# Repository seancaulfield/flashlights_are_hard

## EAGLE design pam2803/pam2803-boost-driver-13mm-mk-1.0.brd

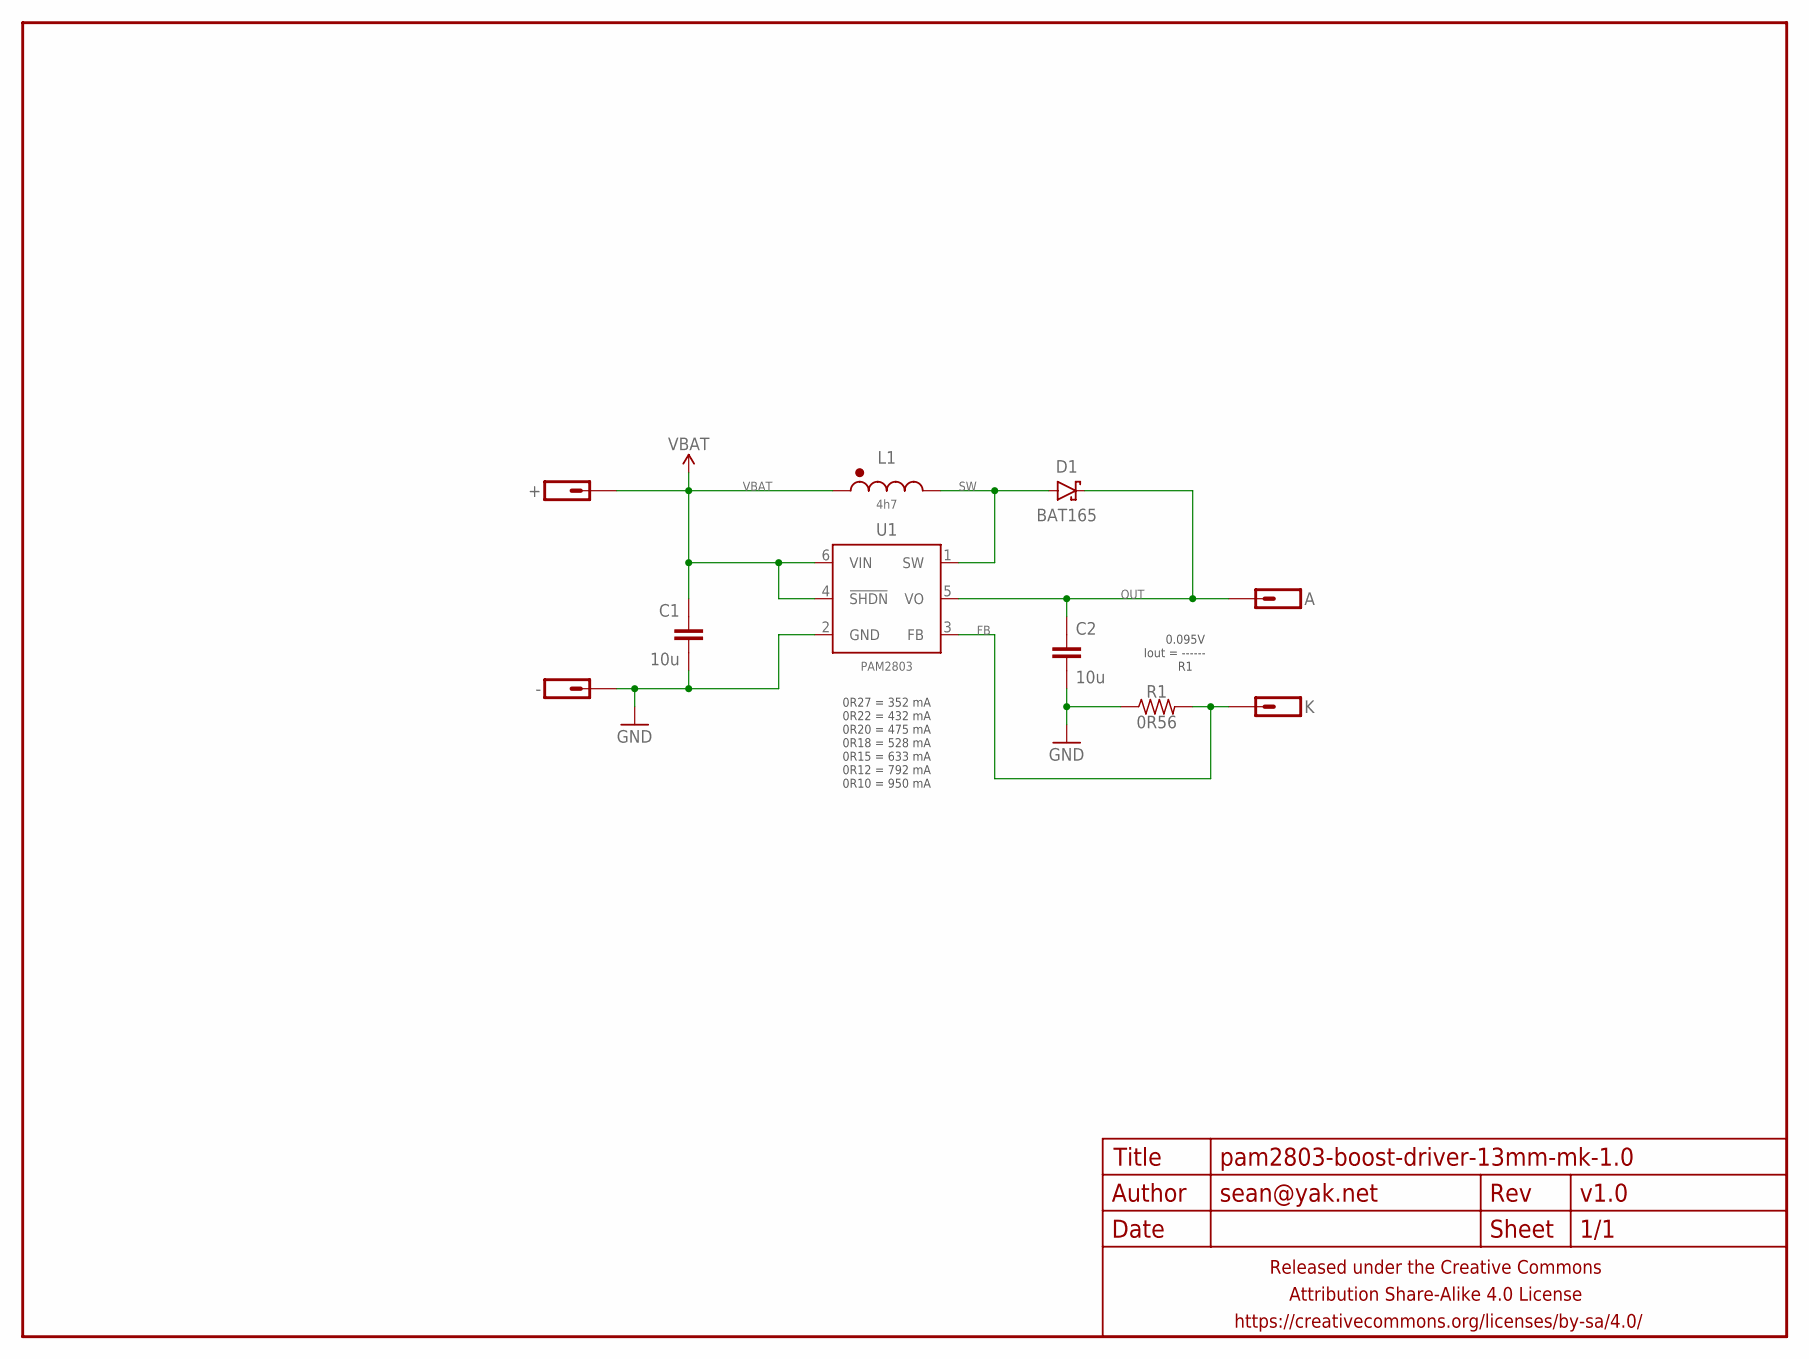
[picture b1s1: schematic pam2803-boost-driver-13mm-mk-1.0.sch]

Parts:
+: M01NOT-A-VIA-NOPE; 1X01_NOSILK_NOSTOP
-: M01NOT-A-VIA-NOPE; 1X01_NOSILK_NOSTOP
A: M01SMD-1.5MM-DIA-NS; 1X01-SMD-1.5MM-DIA-NS
C1, C2: 10u; C0805-TIGHTER
D1: BAT165; SOD323-SCHOTTKY
FRAME1: FRAME-LETTERNO_PACKAGE; DUMMY
K: M01SMD-1.5MM-DIA-NS; 1X01-SMD-1.5MM-DIA-NS
L1: 4h7; EPL2014
R1: 0R56; R0603-TIGHTER
U1: PAM2803; SOT23-6

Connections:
FB: K.P$1, R1.2, U1.3 (FB)
GND: -.P$1, C1.2, C2.2, R1.1, U1.2 (GND)
OUT: A.P$1, C2.1, D1.C, U1.5 (VO)
SW: D1.A, L1.P$2 (2), U1.1 (SW)
VBAT: +.P$1, C1.1, L1.P$1 (1), U1.4 (!SHDN), U1.6 (VIN)

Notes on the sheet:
0.095V Iout = ------ R1
0R27 = 352 mA 0R22 = 432 mA 0R20 = 475 mA 0R18 = 528 mA 0R15 = 633 mA 0R12 = 792 mA 0R10 = 950 mA

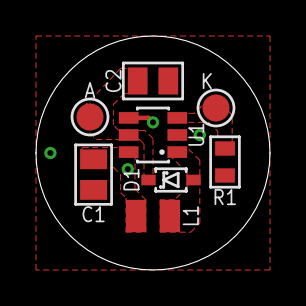
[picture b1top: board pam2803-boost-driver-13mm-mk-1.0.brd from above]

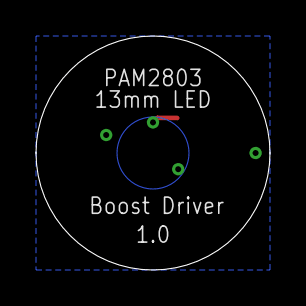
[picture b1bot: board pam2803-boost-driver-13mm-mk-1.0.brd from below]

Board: 2 copper layers, 13.0 x 13.0 mm, 11 parts (2 on the bottom side), 5 nets.

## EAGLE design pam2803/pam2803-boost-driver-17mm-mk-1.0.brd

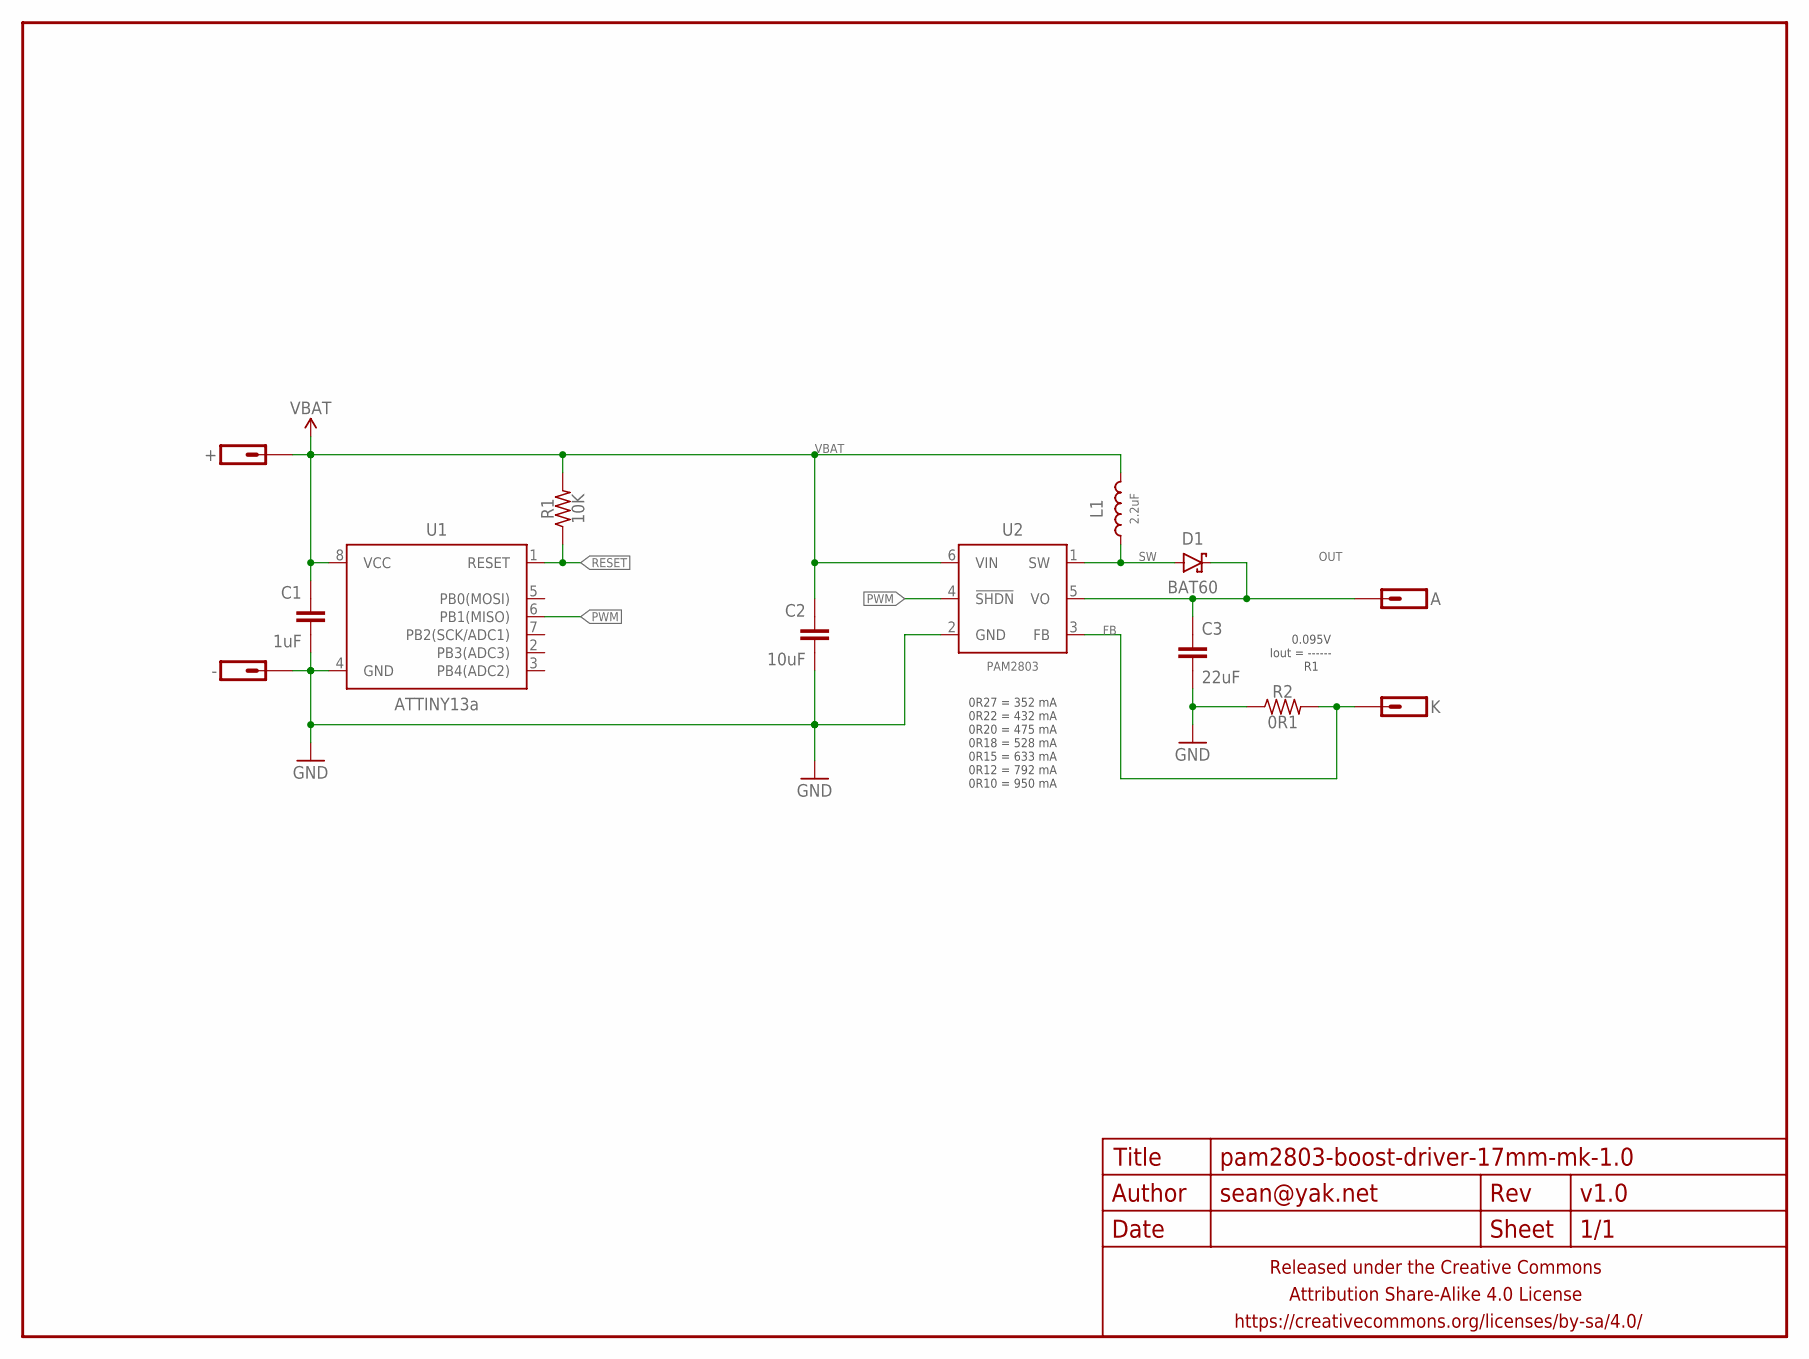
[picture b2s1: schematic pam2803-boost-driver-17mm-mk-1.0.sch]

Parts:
+: M01PTH-1MM-CIR-NS; 1X01-1MM-CIR-NS
-: M01NOT-A-VIA-NOPE; 1X01_NOSILK_NOSTOP
A: M01SMD-1.75DIA; 1X01-SMD-1.75DIA
C1: 1uF; C0603-TIGHTER
C2: 10uF; C0805-TIGHTER
C3: 22uF; C0805-TIGHTER
D1: BAT60; SOD323-SCHOTTKY
FRAME1: FRAME-LETTERNO_PACKAGE; DUMMY
K: M01SMD-1.75DIA; 1X01-SMD-1.75DIA
L1: 2.2uF; XFL4020
R1: 10K; R0603-TIGHTER
R2: 0R1; R0805-TIGHTER
U1: ATTINY13a; SO08-SKINNYPADS
U2: PAM2803; SOT23-6

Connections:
FB: K.P$1, R2.2, U2.3 (FB)
GND: -.P$1, C1.2, C2.2, C3.2, R2.1, U1.4 (GND), U2.2 (GND)
OUT: A.P$1, C3.1, D1.C, U2.5 (VO)
PWM: U1.6 (PB1(MISO)), U2.4 (!SHDN)
RESET: R1.1, U1.1 (RESET)
SW: D1.A, L1.P$2 (2), U2.1 (SW)
VBAT: +.1, C1.1, C2.1, L1.P$1 (1), R1.2, U1.8 (VCC), U2.6 (VIN)

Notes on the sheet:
0.095V Iout = ------ R1
0R27 = 352 mA 0R22 = 432 mA 0R20 = 475 mA 0R18 = 528 mA 0R15 = 633 mA 0R12 = 792 mA 0R10 = 950 mA

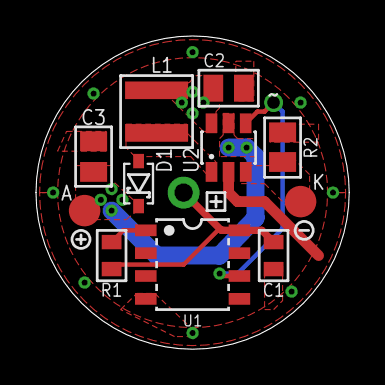
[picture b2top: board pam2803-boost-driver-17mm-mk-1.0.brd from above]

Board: 2 copper layers, 17.4 x 17.4 mm, 14 parts (0 on the bottom side), 7 nets.

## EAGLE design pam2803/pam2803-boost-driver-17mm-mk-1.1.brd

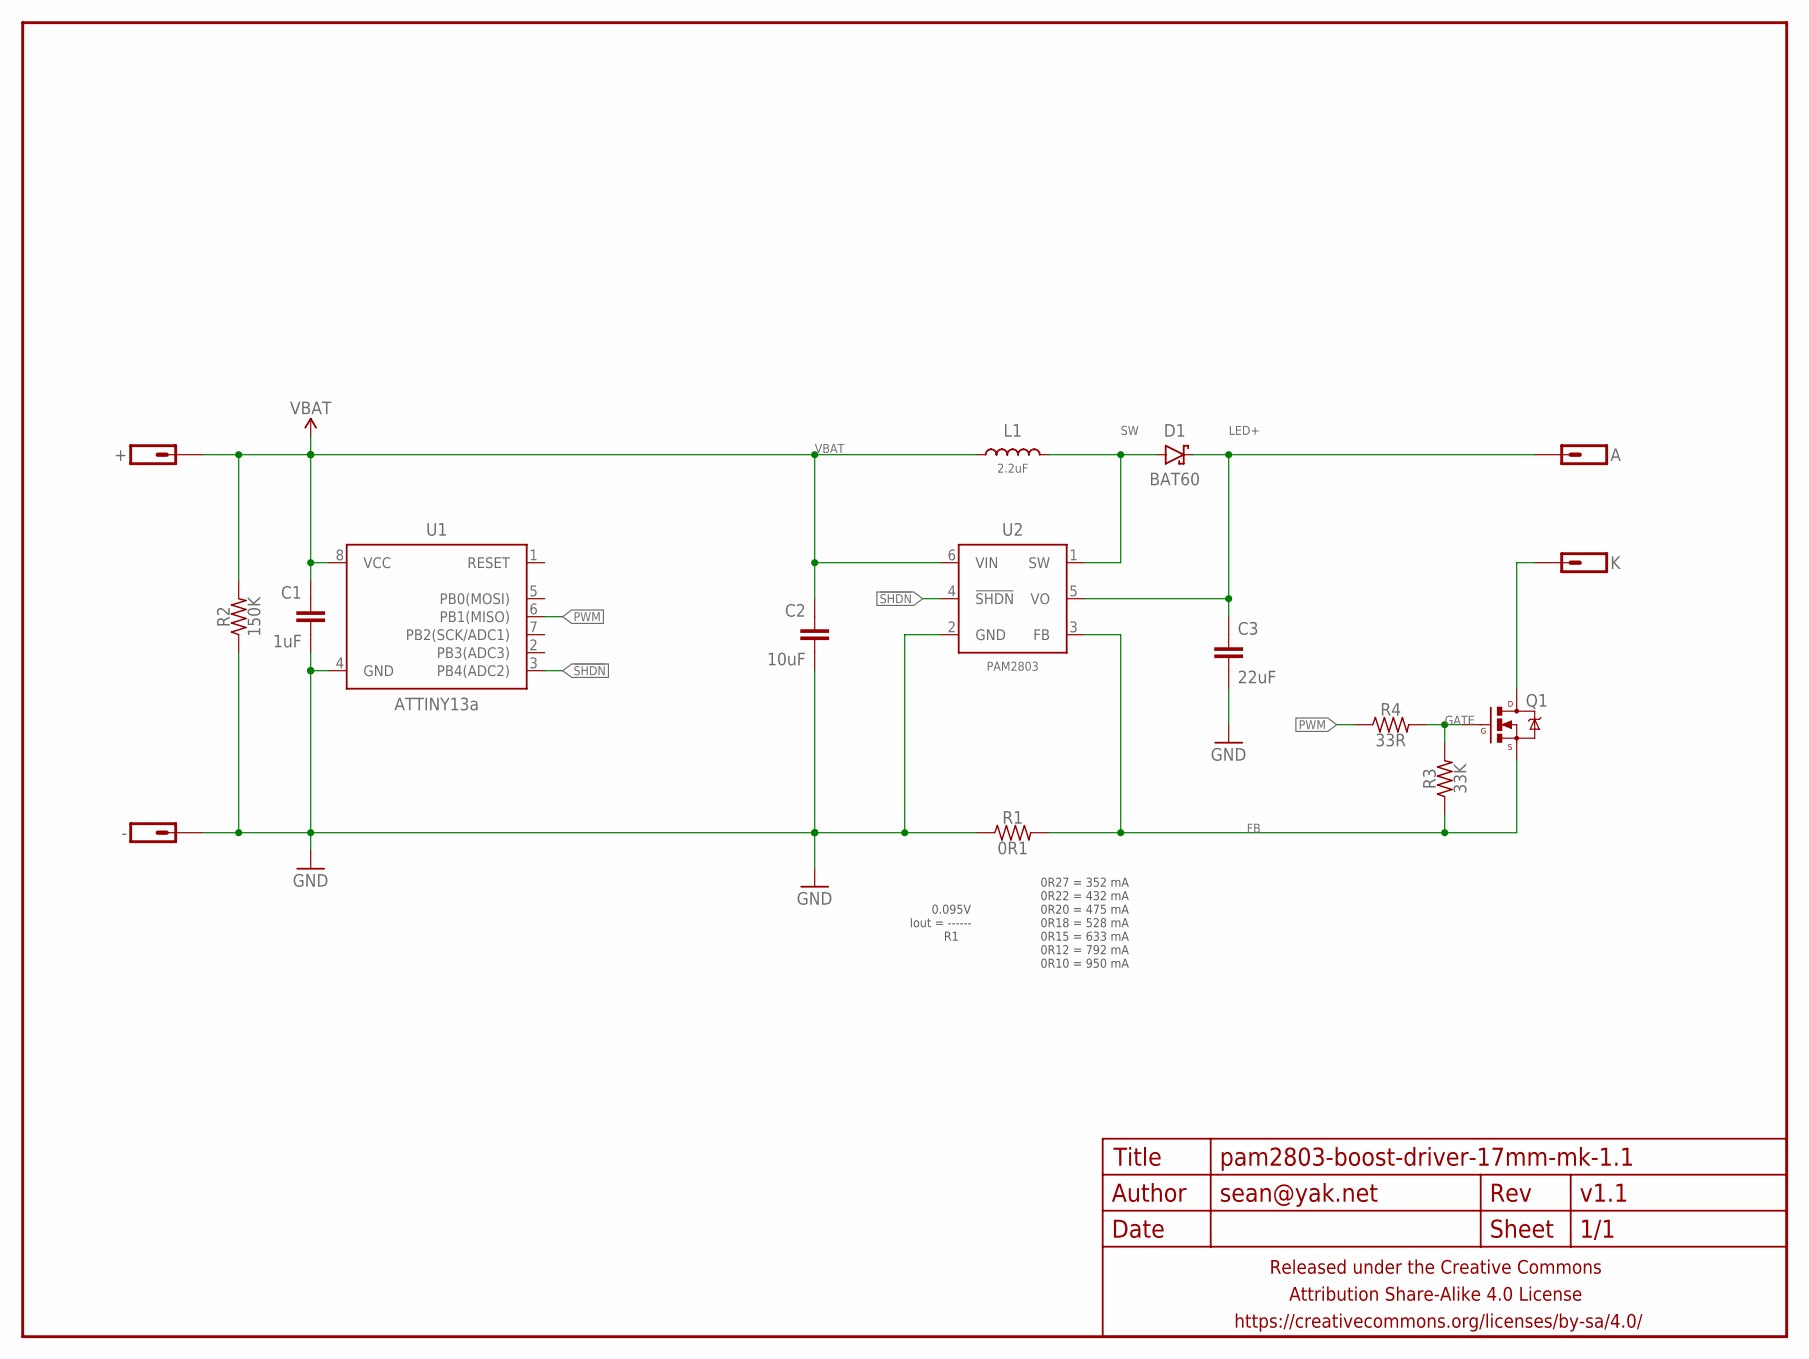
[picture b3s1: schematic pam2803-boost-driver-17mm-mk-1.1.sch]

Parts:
+: M01PTH-1MM-CIR-NS; 1X01-1MM-CIR-NS
-: M01NOT-A-VIA-NOPE; 1X01_NOSILK_NOSTOP
A: M01PTH-1MM-CIR-NS; 1X01-1MM-CIR-NS
C1: 1uF; C0402
C2: 10uF; C0805-TIGHTER
C3: 22uF; C0805-TIGHTER
D1: BAT60; SOD323-SCHOTTKY
FRAME1: FRAME-LETTERNO_PACKAGE; DUMMY
K: M01PTH-1MM-CIR-NS; 1X01-1MM-CIR-NS
L1: 2.2uF; XFL4020
Q1: MOSFET-NCHANNELIRLML2502; SOT23
R1: 0R1; R0805-TIGHTER
R2: 150K; R0603-TIGHTER
R3: 33K; R0603-TIGHTER
R4: 33R; R0603-TIGHTER
U1: ATTINY13a; SO08-SKINNYPADS
U2: PAM2803; SOT23-6

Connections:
!SHDN: U1.3 (PB4(ADC2)), U2.4 (!SHDN)
FB: Q1.2 (S), R1.2, R3.1, U2.3 (FB)
GATE: Q1.1 (G), R3.2, R4.2
GND: -.P$1, C1.2, C2.2, C3.2, R1.1, R2.1, U1.4 (GND), U2.2 (GND)
LED+: A.1, C3.1, D1.C, U2.5 (VO)
LED-: K.1, Q1.3 (D)
PWM: R4.1, U1.6 (PB1(MISO))
SW: D1.A, L1.P$1 (1), U2.1 (SW)
VBAT: +.1, C1.1, C2.1, L1.P$2 (2), R2.2, U1.8 (VCC), U2.6 (VIN)

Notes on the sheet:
0.095V Iout = ------ R1
0R27 = 352 mA 0R22 = 432 mA 0R20 = 475 mA 0R18 = 528 mA 0R15 = 633 mA 0R12 = 792 mA 0R10 = 950 mA

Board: 2 copper layers, 17 parts (3 on the bottom side), 9 nets, no tracks yet.

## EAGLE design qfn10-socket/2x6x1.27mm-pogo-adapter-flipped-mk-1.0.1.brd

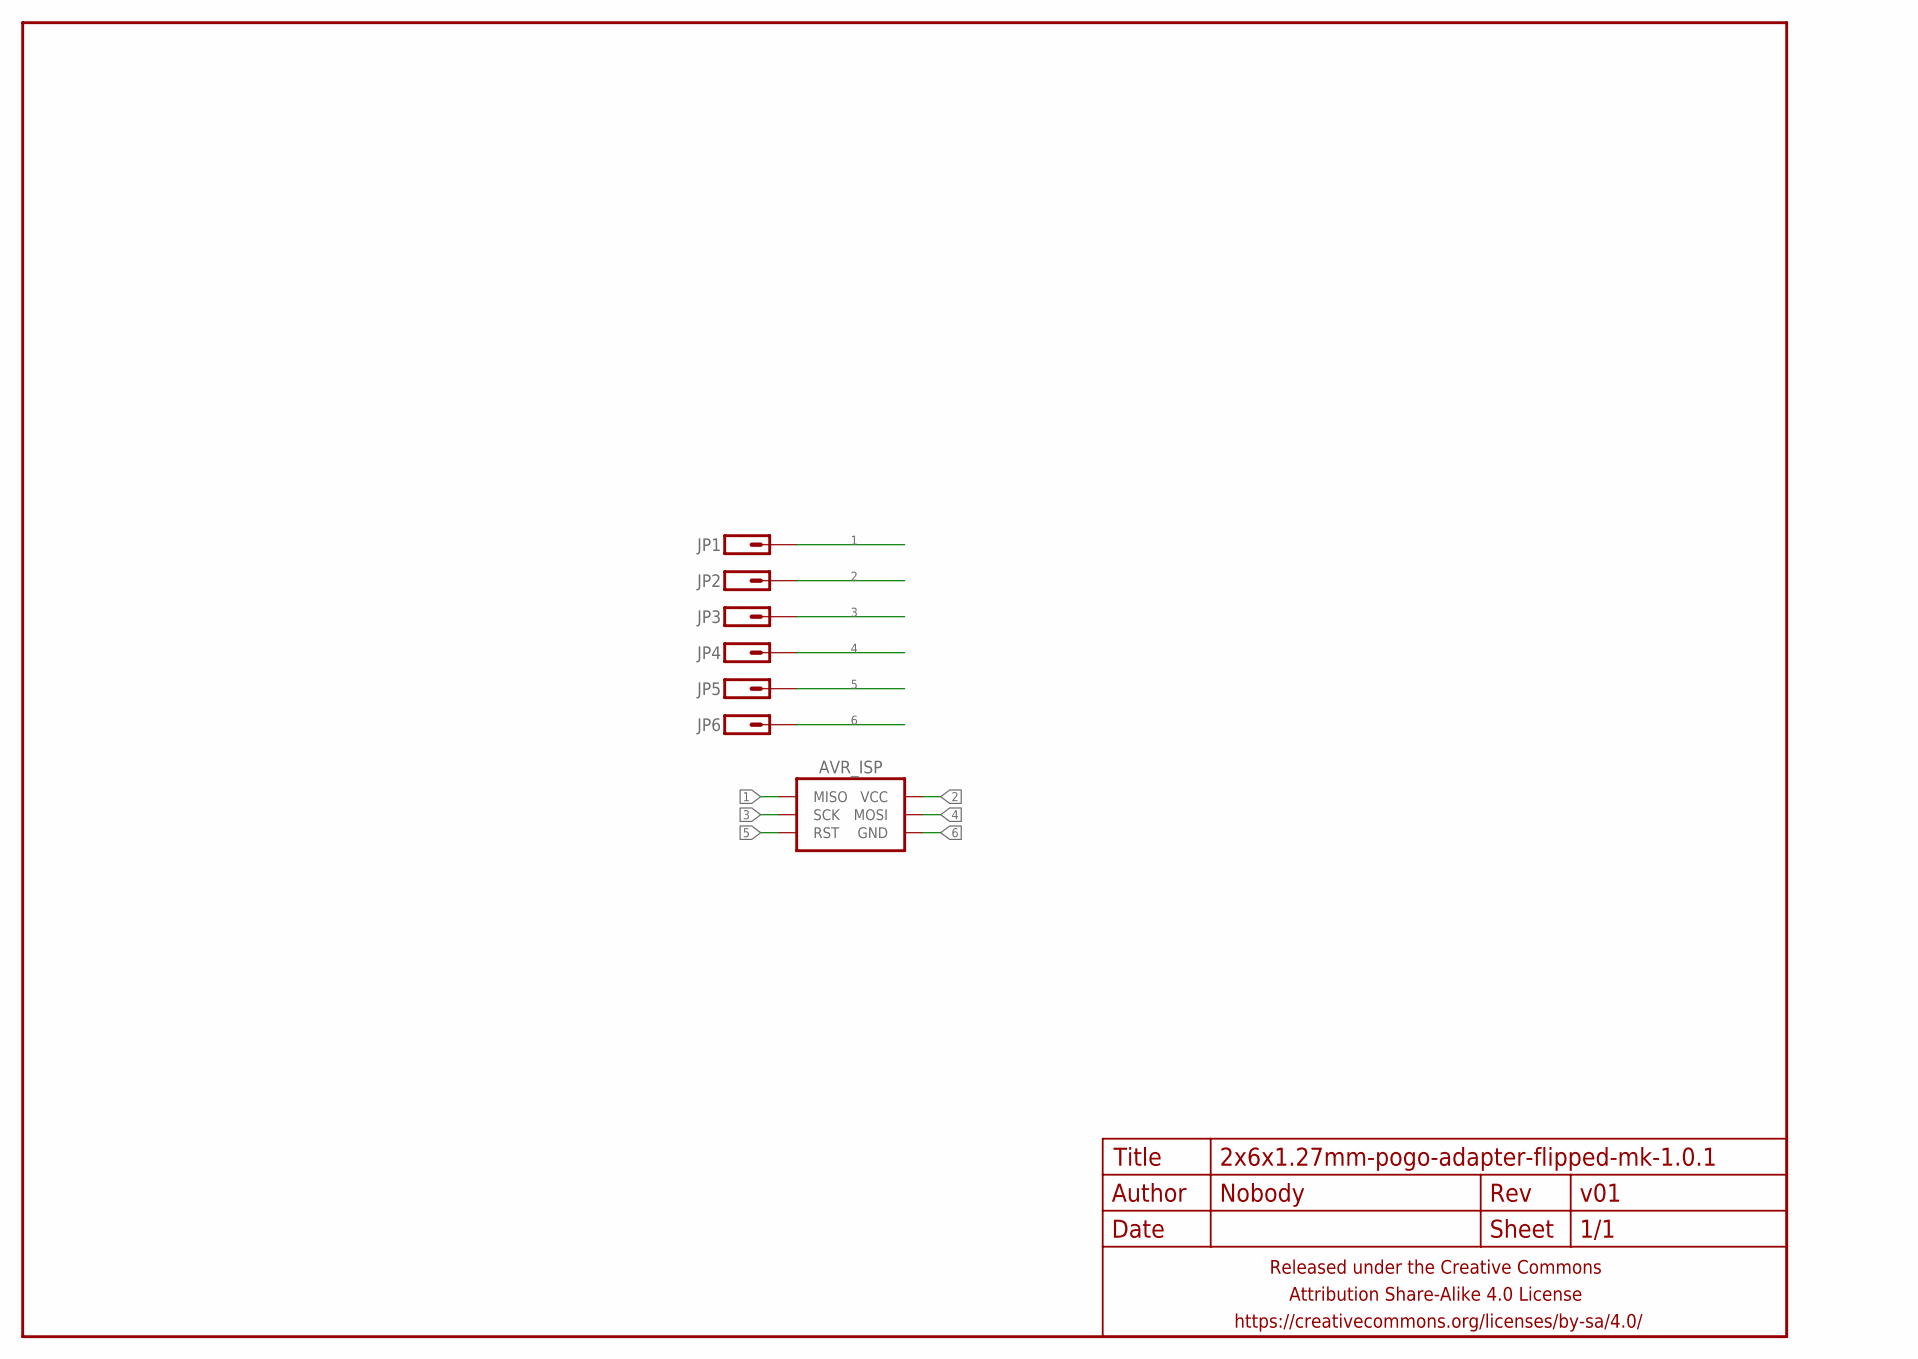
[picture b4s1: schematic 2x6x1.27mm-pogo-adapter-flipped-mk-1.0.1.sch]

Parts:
AVR_ISP: AVR_SPI_PRG_62X3_SMD; 2X3_SMD
FRAME1: FRAME-LETTERNO_PACKAGE; DUMMY
JP1, JP2, JP3, JP4, JP5, JP6: M01PTH-0.7MM-CIR-NS; 1X01-0.7MM-CIR-NS

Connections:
1: AVR_ISP.1 (MISO), JP1.P$1
2: AVR_ISP.2 (VCC), JP2.P$1
3: AVR_ISP.3 (SCK), JP3.P$1
4: AVR_ISP.4 (MOSI), JP4.P$1
5: AVR_ISP.5 (RST), JP5.P$1
6: AVR_ISP.6 (GND), JP6.P$1

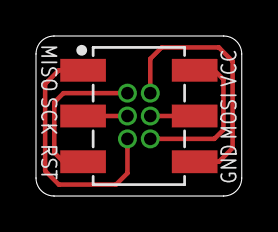
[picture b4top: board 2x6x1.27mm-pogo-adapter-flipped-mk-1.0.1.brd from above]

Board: 2 copper layers, 11.4 x 8.9 mm, 8 parts (0 on the bottom side), 6 nets.

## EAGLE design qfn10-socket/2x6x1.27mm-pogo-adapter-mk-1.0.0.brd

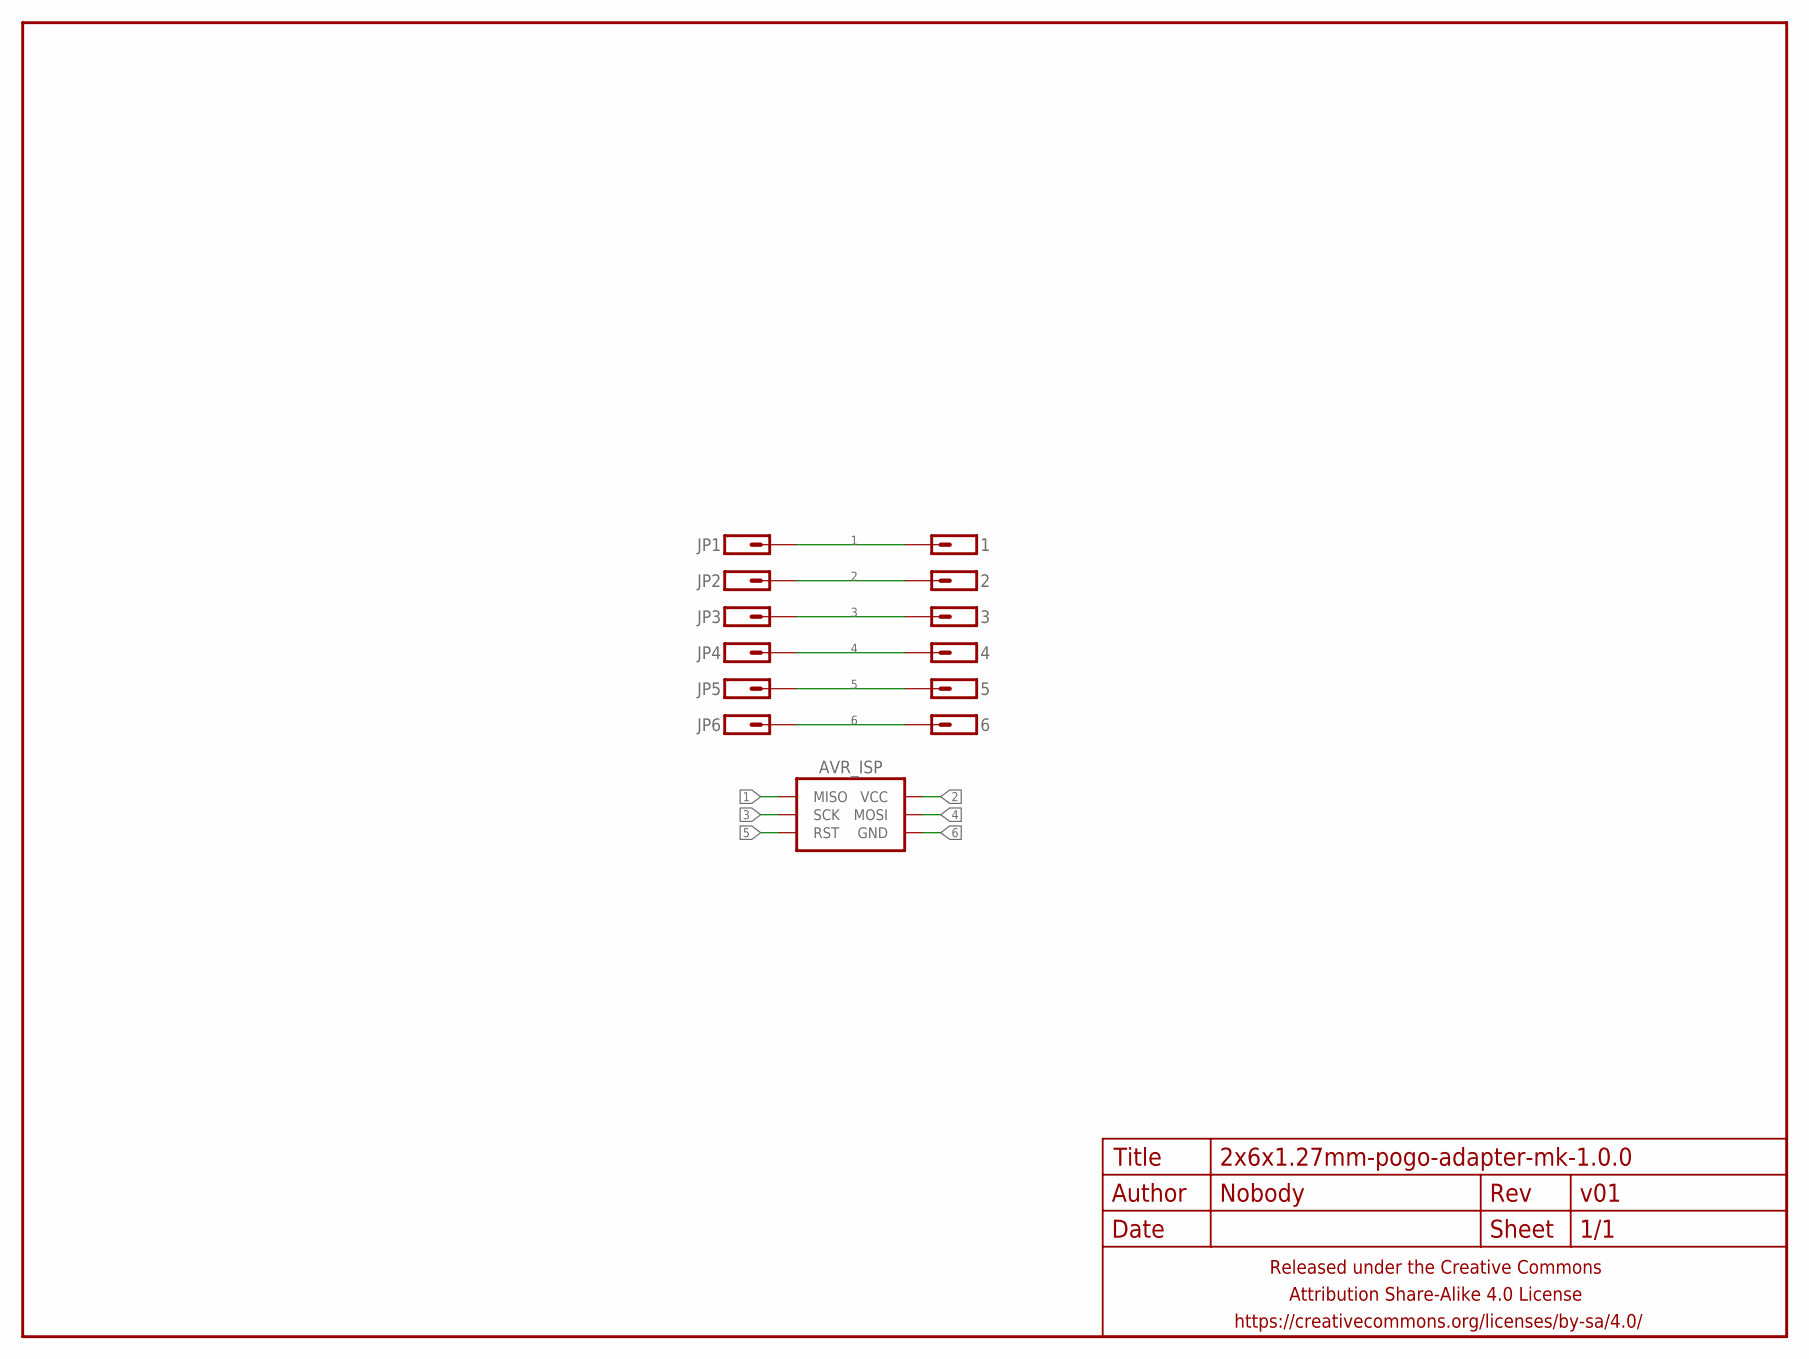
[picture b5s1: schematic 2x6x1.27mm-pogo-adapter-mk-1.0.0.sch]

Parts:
1, 2, 3, 4, 5, 6: M01PTH; 1X01
AVR_ISP: AVR_SPI_PRG_6PTH-SHROUD-ALT; 2X3-SHROUDED-ALT
FRAME1: FRAME-LETTERNO_PACKAGE; DUMMY
JP1: M01PTH-0.7MM-CIR-NS; 1X01-0.7MM-CIR-NS
JP2, JP3, JP4, JP5, JP6: M01PTH-0.65MM-NS; 1X01_635MM

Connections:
1: 1.1, AVR_ISP.1 (MISO), JP1.P$1
2: 2.1, AVR_ISP.2 (VCC), JP2.P$1
3: 3.1, AVR_ISP.3 (SCK), JP3.P$1
4: 4.1, AVR_ISP.4 (MOSI), JP4.P$1
5: 5.1, AVR_ISP.5 (RST), JP5.P$1
6: 6.1, AVR_ISP.6 (GND), JP6.P$1

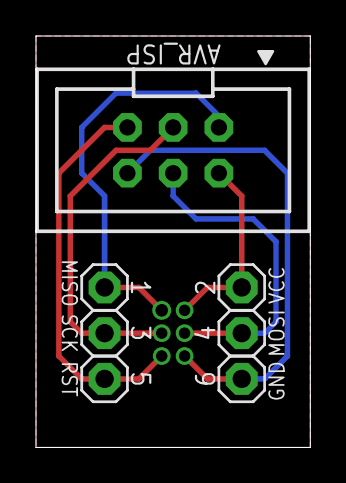
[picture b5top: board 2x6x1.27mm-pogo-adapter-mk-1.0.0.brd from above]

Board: 2 copper layers, 15.2 x 22.9 mm, 14 parts (0 on the bottom side), 6 nets.

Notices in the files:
parts and their libraries:
a_parts: Released under the Creative Commons Attribution Share-Alike 4.0 License
a_parts: https://creativecommons.org/licenses/by-sa/4.0
a_parts: Released under the Creative Commons
